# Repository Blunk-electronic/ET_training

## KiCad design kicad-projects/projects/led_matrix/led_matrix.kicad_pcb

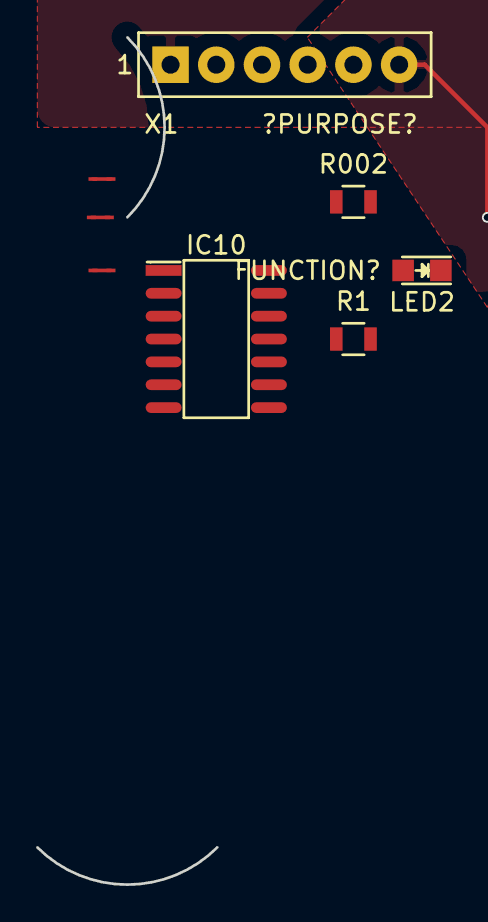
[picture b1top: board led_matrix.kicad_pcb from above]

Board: 4 copper layers, 9 parts (1 on the bottom side), 7 nets.

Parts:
IC2: 74193; S_SO16
IC10: 7400; S_SO14
LED2: red; S_0805
N1, N2, N3: NETCHANGER; 0mm2
R1: 100R; S_0805
R002: 220R; S_0805
X1: FEMALE_01X06; T_FEMALE_01X06_VERTICAL_PITCH_2mm54

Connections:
/IN: IC10.1, IC10.2, X1.3
/LED_ANODE: LED2.A, R1.2
/OUT: IC10.8, N1.1, N2.1, N3.1, R002.1, X1.2
/OUT#: IC10.3, IC10.9, IC10.10, X1.4
GND: IC10.7, LED2.C, R002.2, X1.1
unnamed: IC2.11, IC2.14
VCC: IC2.8, IC2.16, IC10.14, R1.1, X1.6

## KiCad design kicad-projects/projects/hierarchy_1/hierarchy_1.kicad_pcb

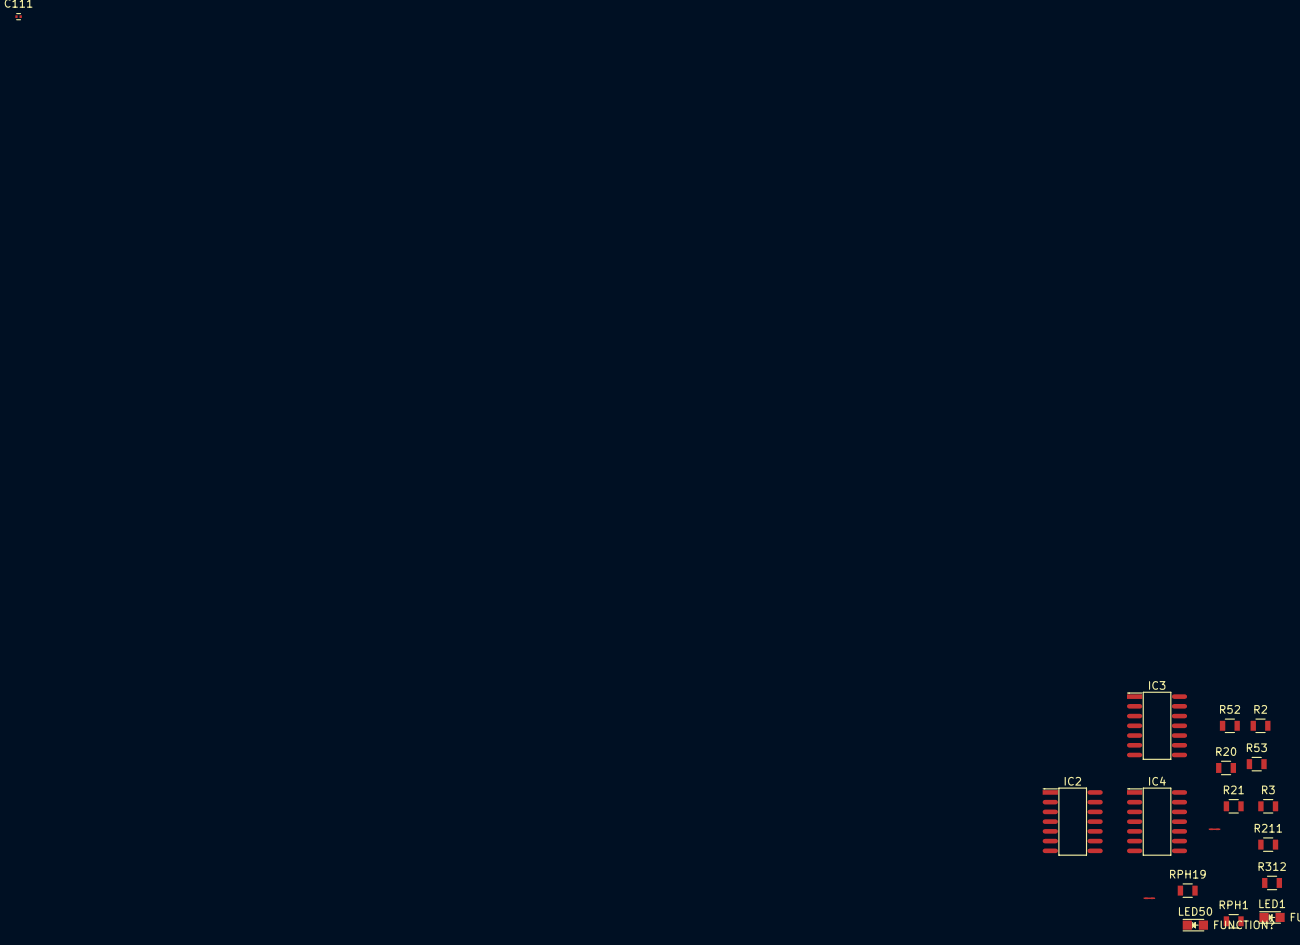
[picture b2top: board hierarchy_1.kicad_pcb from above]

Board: 2 copper layers, 18 parts (0 on the bottom side), 16 nets, no tracks yet.

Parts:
C111: 100n; S_0201
IC2, IC3, IC4: 7400; S_SO14
LED1, LED50: red; S_0805
N1, N2: NETCHANGER; 0mm2
R2, R3, R211, R312: 330R; S_0805
R20, R21, R52, R53: 1k2; S_0805
RPH1, RPH19: 100R; S_0805

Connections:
/TOP_GND: R3.1, R312.1
/TOP_VCC: R2.2, R211.2
/core/LEVEL_SHIFTER/logic_ls/Q: IC4.2, IC4.11
/core/LEVEL_SHIFTER/logic_ls/Q_N: IC4.3, IC4.13
/driver1/GND_LOCAL: R20.2, R21.1
/driver2/GND_LOCAL: R52.2, R53.1
/logic1/Q: IC2.2, IC2.11
/logic1/Q_N: IC2.3, IC2.13
/logic2/Q: IC3.2, IC3.11
/logic2/Q_N: IC3.3, IC3.13
DRV_1: LED1.A, LED50.A, N1.2, R20.1, R52.1
DRV_2: LED1.C, LED50.C, N2.2, R21.2, R53.2
GND: IC2.7, IC3.7, IC4.7
SENSE_1: N1.1, R2.1, R211.1, RPH1.1, RPH19.1
SENSE_2: N2.1, R3.2, R312.2, RPH1.2, RPH19.2
VCC: IC2.14, IC3.14, IC4.14

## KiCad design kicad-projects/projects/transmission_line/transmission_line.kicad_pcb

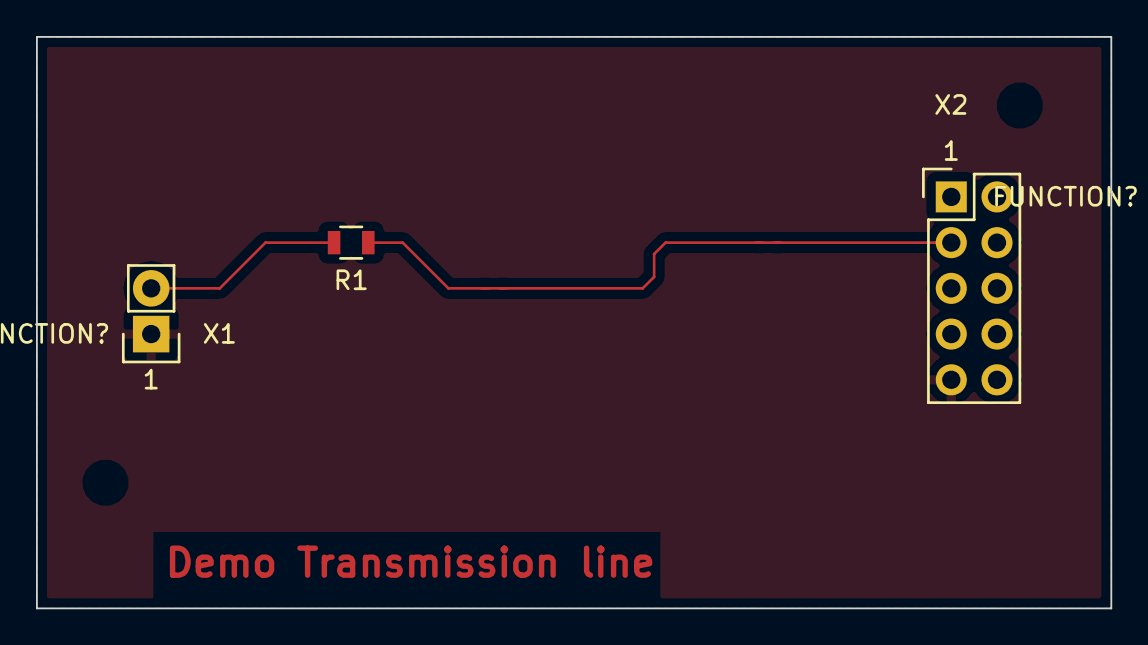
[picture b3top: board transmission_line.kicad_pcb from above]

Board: 2 copper layers, 59.7 x 31.8 mm, 5 parts (0 on the bottom side), 5 nets.

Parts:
N1, N2: NetChanger; N_0.15MM
R1: 100R; R_S_0805
X1: CONN_01X02; X_PAC_T_MALE_2X1_VERTICAL_GRID_2.54MM
X2: CONN_02X05; X_PAC_T_MALE_2X5_VERTICAL_GRID_2.54MM

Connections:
/GND: X1.1, X2.9
/NET_A: R1.2, X1.2
/NET_B: N1.1, R1.1
/NET_C: N1.2, N2.1
/NET_D: N2.2, X2.3

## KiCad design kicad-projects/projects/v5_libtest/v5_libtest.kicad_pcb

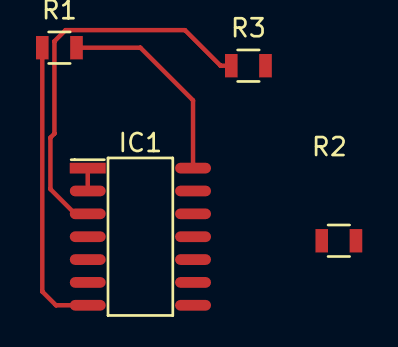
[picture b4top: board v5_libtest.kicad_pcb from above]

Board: 2 copper layers, 4 parts (0 on the bottom side), 5 nets.

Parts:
IC1: 7400; S_SO14
R1, R2, R3: 100R; S_0805

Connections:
GND: IC1.7, R1.1
unnamed: IC1.1, IC1.2, R2.1
unnamed: IC1.3, R3.1
unnamed: R2.2, R3.2
VCC: IC1.14, R1.2

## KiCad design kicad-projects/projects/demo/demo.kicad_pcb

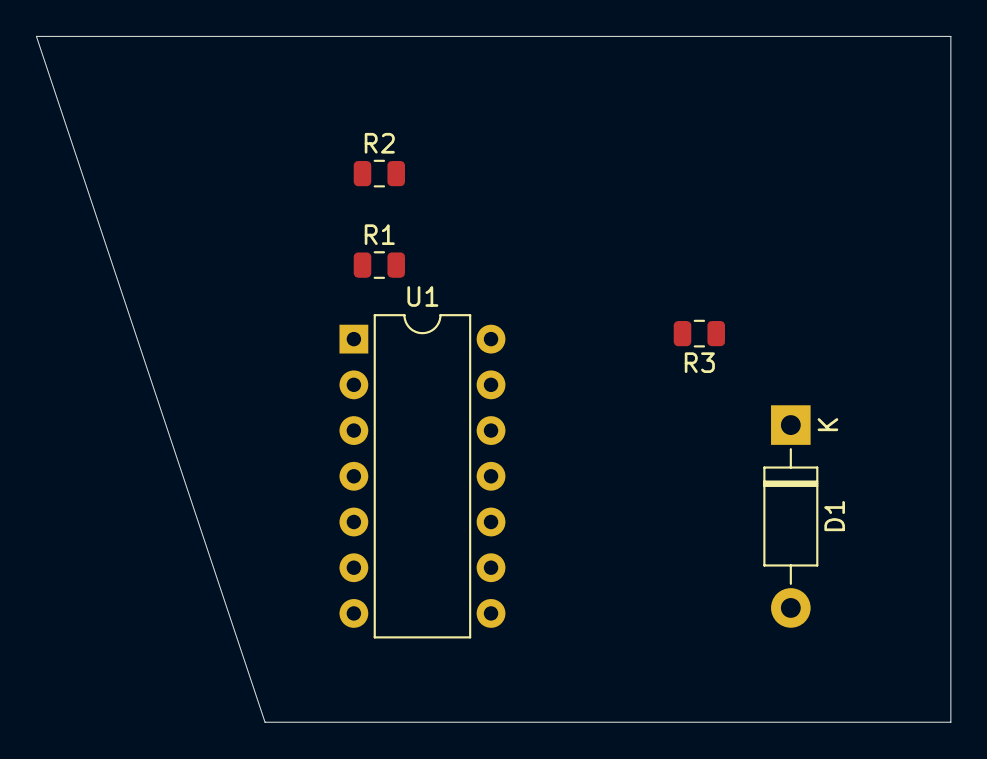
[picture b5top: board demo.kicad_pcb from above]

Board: 2 copper layers, 50.8 x 38.1 mm, 5 parts (0 on the bottom side), 5 nets, no tracks yet.

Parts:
D1: 1N4001; D_DO-41_SOD81_P10.16mm_Horizontal
R1, R2, R3: 1k; R_0805_2012Metric
U1: 7400; DIP-14_W7.62mm

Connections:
GND: R1.2, R2.2, R3.2
unnamed: D1.1, R3.1
unnamed: D1.2, U1.3
unnamed: R1.1, U1.1
unnamed: R2.1, U1.2

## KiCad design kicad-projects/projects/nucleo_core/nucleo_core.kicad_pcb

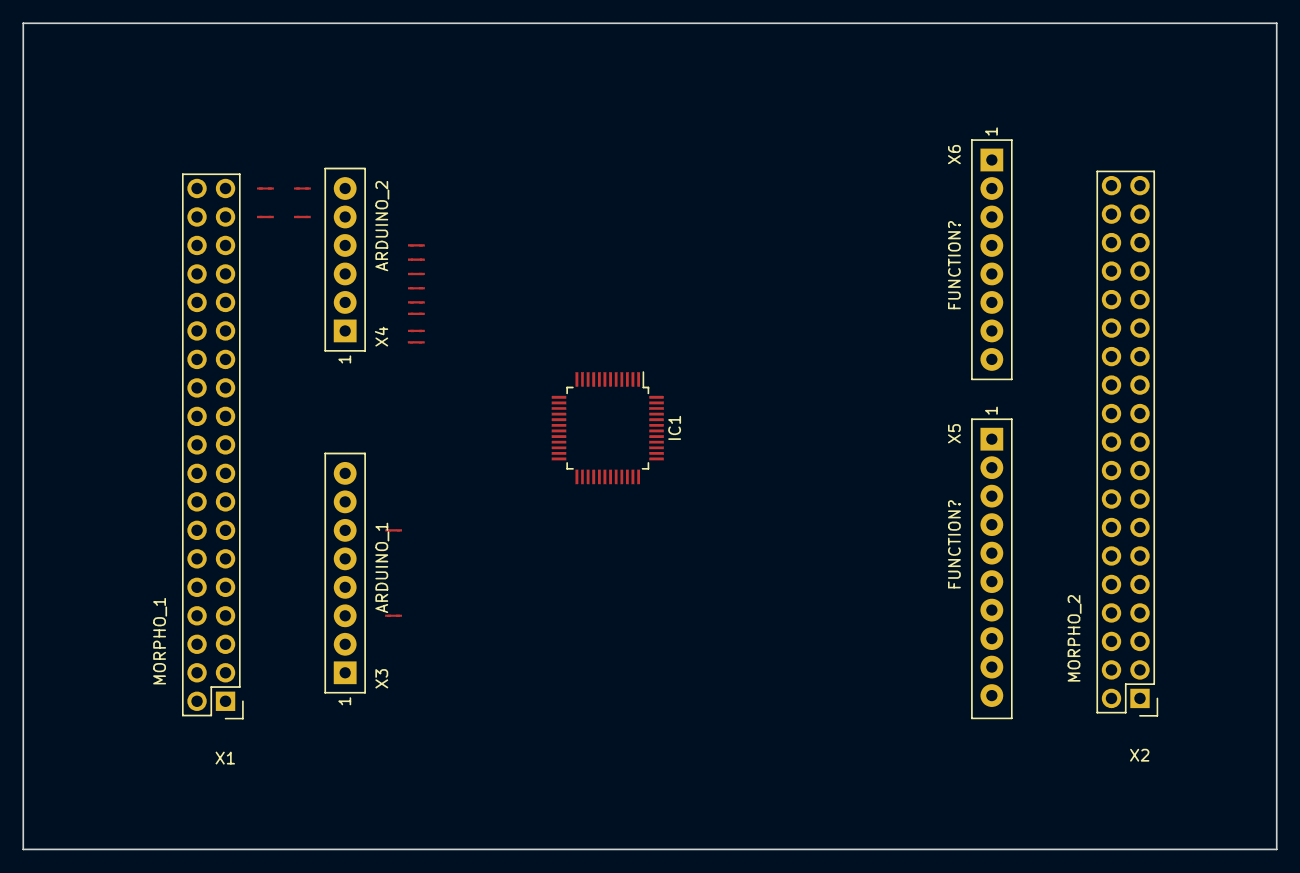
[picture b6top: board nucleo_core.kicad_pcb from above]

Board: 2 copper layers, 111.8 x 73.7 mm, 21 parts (0 on the bottom side), 23 nets, no tracks yet.

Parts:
IC1: STM32F030C6Tx; LQFP-48_7x7mm_Pitch0.5mm
N601, N602, N603, N604, N605, N606, N607, N701, N702, N703, N704, N705, N706, N707: NetChanger; N_0.2MM
X1, X2: FEMALE_02X19; X_PAC_T_MALE_2X19_VERTICAL_GRID_2.54MM
X3, X6: FEMALE_01X08; X_PAC_T_FEMALE_1X8_VERTICAL_GRID_2.54MM
X4: FEMALE_01X06; X_PAC_T_FEMALE_1X6_VERTICAL_GRID_2.54MM
X5: FEMALE_01X10; X_PAC_T_FEMALE_1X10_VERTICAL_GRID_2.54MM

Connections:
ARDU_A0: N702.1, X4.1
ARDU_A1: N703.1, X4.2
ARDU_A2: N704.1, X4.3
ARDU_A3: N705.1, X4.4
ARDU_A4: N706.1, X4.5
ARDU_A5: N707.1, X4.6
ARDU_RST_N: N701.1, X3.3
GND: X3.6, X3.7
MCU_PA0: IC1.10, N602.2, N702.2
MCU_PA1: IC1.11, N603.2, N703.2
MCU_PA4: IC1.14, N604.2, N704.2
MCU_PB0: IC1.18, N605.2, N705.2
MCU_RST_N: IC1.7, N601.2, N701.2
MORPHO_A4: N606.1, X1.36
MORPHO_A5: N607.1, X1.38
MORPHO_ARDU_A4: N606.2, N706.2
MORPHO_ARDU_A5: N607.2, N707.2
MORPHO_PA0: N602.1, X1.28
MORPHO_PA1: N603.1, X1.30
MORPHO_PA4: N604.1, X1.32
MORPHO_PB0: N605.1, X1.34
MORPHO_RST_N: N601.1, X1.14
P3V3: X3.2, X3.4

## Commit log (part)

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2019-03-04 ignore file for reports
2019-03-05 netchanger ports
2019-03-06 propose script
2019-03-06 changed move relative
2019-03-07 rename net and device
2019-03-14 test reading segments
2019-03-14 rework net segment positions
2019-03-15 fix strand positions
2019-03-15 test moving unit
2019-03-19 test integrity check
2019-03-29 test rotation
2019-04-03 start add device
2019-04-07 test add devcie
2019-04-17 test invoke
2019-04-24 test rename net
2019-04-25 test delete net and segment
2019-04-25 test drag segment
2019-04-26 test dragging net segments
2019-04-27 test catch zone when dragging net segments
2019-04-27 test dragging segments and connecting ports
2019-04-30 test draw net
2019-05-03 test strand merge
2019-05-03 test add netchanger
2019-05-03 test delete netchanger
2019-05-04 test move netchanger
2019-05-07 test rotate netchanger
2019-05-07 comments in example script
2019-05-09 test add submodule
2019-05-10 test saving modules
2019-05-16 test add port
2019-05-17 test delete submodule port
2019-05-18 test move submodule port
2019-05-20 test drag submodule port
2019-05-21 test delete submodule
2019-05-23 test drag submodule
2019-05-28 test copy device and submodule
2019-05-29 test set file submodule
2019-06-01 test net labels
2019-06-06 propose section for assembly variants
2019-06-07 test assy variants
2019-06-11 create, delete and describe assembly variant
2019-06-14 test assembly variants with devices
2019-06-14 variants in submodule and conf file
2019-06-17 test mount and remove submodule
2019-06-17 test assign numbering offset
2019-06-18 test rename submodule
2019-06-22 test assembly variant in conf file
2019-06-25 test build submodule tree
2019-06-26 test device index ranges
2019-06-28 test auto set of device offsets
2019-07-05 test make bom
2019-07-09 test make netlist
2019-07-26 test board ops
2019-07-27 test make pick and place
2019-07-29 test pick and place
2019-07-29 test move submodule
2019-07-31 test pick and place complete
2019-08-01 add submodule port with direction
2019-08-05 text make netlist
2019-08-07 test save module
2019-08-10 test netlist export
2019-08-13 test set net scope
2019-08-19 add more test scripts
2019-08-20 clean up
2019-08-20 test draw line
2019-08-20 test draw board outline
2019-08-21 test draw tracks
2019-08-22 test route net and freetrack
2019-08-22 test delete outline
2019-09-06 replace keyword reference by name
2019-09-06 test delete board outline
2019-09-06 test ripup signal line
2019-09-06 test ripup freetrack
2019-09-06 test draw silk line and arc
2019-09-07 test draw silk circle
2019-09-10 test hatched circles
2019-09-11 test flip package
2019-09-13 test route terminal to point
2019-09-14 test drawing grid
2019-09-14 test drawing and deleting assy doc
2019-09-16 test add layer
2019-09-16 test keepout
2019-09-16 test stop mask
2019-09-17 test delete layer
2019-09-18 test route restrict
2019-09-18 test via restrict
2019-09-18 rework keepout circles
2019-09-19 test stencil
2019-10-07 test routing
2019-10-08 test cutout zone
2019-10-09 fix signal layer
2019-10-10 test cutouts
2019-10-18 abandon concept of text width. there is only text size
2019-10-18 fix line widths
2019-10-30 rework appearance
2019-11-08 add link to frames
2019-11-09 add meta data
2019-11-11 active assembly variant moved to section assembly_variants
2019-11-11 test date and time
2020-01-09 fix position of title block
2020-01-15 test arc direction
2020-01-17 test grid
2020-01-30 test board frame
2020-02-04 test draw silk screen
2020-02-05 test silk screen
2020-02-17 change text size
2020-02-26 test rotation of placeholders
2020-03-06 test show module
2020-03-07 test board origin
2020-03-28 test tag labels
2020-03-30 test invoke unit
2020-03-31 test port names
2020-04-02 test unit rotation
2020-04-04 test adding submodule ports
2020-04-07 remove text styles
2020-04-07 remove line width
2020-04-09 test indexes
2020-04-10 test sheet descriptions
2020-04-15 test cam markers
2020-04-17 test conductor layers
2020-04-20 test scripting via gui
2020-04-22 test zoom
2020-04-23 test zoom to point
2020-04-23 test displaying layers
2020-04-27 a useful frame template
2020-04-28 change frame
2020-04-29 test vias
2020-04-30 test layer stack
2020-05-04 test flip
2020-05-08 test polygon
2020-05-09 test polygons
2020-05-11 commented corrupted arcs
2020-05-14 test package assy doc
2020-05-15 test fill
2020-05-16 test overlaps of lines
2020-05-16 test fill zone in stencil
2020-05-18 test layer check
2020-05-19 test package via restrict
2020-05-20 test draw terminal name
2020-05-20 test pad rotation
2020-05-21 test plated millings
2020-05-21 test drilled hole
2020-05-26 test draw placeholder
2020-06-09 test placeholders and texts
2020-06-09 test upper case letters
2020-06-09 test bench single-led
2020-06-10 play with fill pattern
2020-06-10 test pattern
2020-06-11 text digits
2020-06-12 test text completed
2020-06-12 start demo
2020-06-13 fix resistor variant
2020-06-17 place connector
2020-06-27 test non-electric devices
2020-07-01 dummy project file
2020-07-01 dummy dru file
2020-07-01 test dru file
2020-07-02 test DRU
2020-07-03 project configuration file
2020-07-06 move dru file
2020-07-08 schematic A4 frame
2020-07-08 draw nets
2020-07-09 add dru files
2020-07-22 add kicad test projects
2020-08-29 test drawing nets
2020-11-05 test place internal unit
2020-11-27 test delete module
2020-12-11 test coupon
2020-12-11 test route net
2020-12-11 texts in assy doc
2020-12-12 sheet descriptions
2020-12-12 test place text
2020-12-29 text text in restrict layers
2020-12-30 fix texts
2020-12-30 rename copper to conductor
2021-01-05 delta size for restring
2021-01-09 test draw via layer numbers
2021-01-12 test user settings for vias
2021-01-15 test blind vias
2021-01-27 test polygon settings
2021-02-02 play with cairo operators
2021-02-04 test route command
2021-02-08 test fill polygon command
2021-02-23 test on_board function
2021-03-11 test filling polygon
2021-03-11 test filling polygons
2021-04-15 test fill lines
2021-05-22 test holes
2021-05-26 rework entry mode of polygons
2021-09-29 test hatched fill
2021-10-23 test
2021-12-03 start demo project thermostat
2021-12-11 test ratsnets
2022-03-23 thermostat
2022-03-23 demo
2022-05-18 test offset polygon
2022-07-18 test cropping
2022-10-05 test filling around buried vias
2022-10-19 dummy text
2022-11-07 test fill around unconnected terminals
2022-11-23 test thermal symbol
2022-12-02 testbench for lib models
2022-12-06 test relief linewidth
2022-12-10 test fill-zone-fail scenario
2022-12-15 test resistors an capacitors
2023-01-06 test drawing conductor objects
2023-01-21 tag label
2023-03-24 proper placement
2023-05-06 test silkscreen
2024-06-25 grid test
2024-10-04 fix fame position
2024-11-27 frequently used test commands
2024-11-28 fix grid
2024-11-28 test bounding-box
2024-11-29 change section SILK_SCREEN to SILKSCREEN
2024-11-29 change section STOP_MASK to STOPMASK
2024-12-09 fix command to draw route restrict objects
2024-12-09 test route and via restrict zone
2025-01-25 add placeholders in pcb
2025-03-01 test stencil zone command
2025-03-28 add placeholders
2025-03-28 test board outline
2025-06-18 test connection of segment with port
2025-07-14 test nested scripts
2025-08-27 test unit fetch
2025-11-05 add conventions file
2025-11-12 test moving package placeholder
2025-11-28 restart demo module
2025-11-28 separate test module 'demo_test'
2025-11-28 restore demo module
2025-11-28 add logic block
2025-12-02 add high voltage block
2025-12-03 Add fiducial, mounting holes and GND mark
2025-12-13 route net PWR_ON_LED_A
2025-12-20 fix partcodes, test fill zones
2025-12-22 add track on bottom side
2025-12-23 add mark for screw
2025-12-30 add fixture alignment
2025-12-30 add floating fill zone
2025-12-31 add solder paste pads for fixture
2025-12-31 add stop mask lines in floating conductor zone
2025-12-31 add stop mask zone and text in floating conductor zone
2026-01-23 rename and create modules
2026-01-23 save test-scripts
2026-01-24 test adding library paths
2026-01-24 test drawing mirrored vector text
2026-01-24 add placeholder for module name in bottom silkscreen
2026-01-26 test mirrored assembly doc text
2026-02-04 test arcs in board outline
2026-03-04 test netchanger direction
2026-03-24 test netchanger commands
2026-03-31 test set signal layer
2026-04-08 fix netchanger coordinates
2026-04-08 test deleting sheets
2026-04-11 move netchanger
2026-04-15 prepare submodule oscillator
2026-04-15 prepare submodule tests
2026-05-01 add AGND test structure
2026-05-08 test submodule instance
2026-05-08 add test scripts
2026-05-11 test show non-electrical device
2026-05-12 test delete unit
